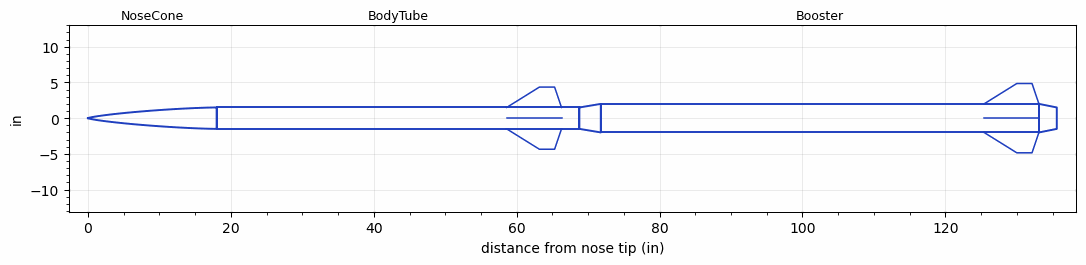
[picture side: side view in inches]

<RASAeroDocument>
 <FileVersion>2</FileVersion>
 <RocketDesign>
  <NoseCone>
   <Length>18</Length>
   <Diameter>3</Diameter>
   <Shape>Von Karman Ogive</Shape>
   <Location>0</Location>
  </NoseCone>
  <BodyTube>
   <Length>50.77</Length>
   <Diameter>3</Diameter>
   <Location>18</Location>
   <Fin>
    <Count>4</Count>
    <Chord>7.675</Chord>
    <Span>2.85</Span>
    <SweepDistance>4.579</SweepDistance>
    <TipChord>2.13</TipChord>
    <Thickness>0.125</Thickness>
    <LERadius>0.08</LERadius>
    <Location>10.175</Location>
    <AirfoilSection>Hexagonal</AirfoilSection>
    <FX1>0.22</FX1>
    <FX3>0.25</FX3>
   </Fin>
  </BodyTube>
  <Booster>
   <Length>61.32</Length>
   <Diameter>4</Diameter>
   <InsideDiameter>3</InsideDiameter>
   <Location>68.77</Location>
   <ShoulderLength>3</ShoulderLength>
   <BoattailLength>2.5</BoattailLength>
   <BoattailRearDiameter>3</BoattailRearDiameter>
   <Fin>
    <Count>4</Count>
    <Chord>7.675</Chord>
    <Span>2.85</Span>
    <SweepDistance>4.58</SweepDistance>
    <TipChord>2.13</TipChord>
    <Thickness>0.125</Thickness>
    <LERadius>0.08</LERadius>
    <Location>7.675</Location>
    <AirfoilSection>Hexagonal</AirfoilSection>
    <FX1>0.22</FX1>
    <FX3>0.25</FX3>
   </Fin>
  </Booster>
  <Surface>Rough Camouflage Paint</Surface>
  <ModifiedBarrowman>True</ModifiedBarrowman>
  <Turbulence>True</Turbulence>
  <UseBooster1>False</UseBooster1>
  <UseBooster2>False</UseBooster2>
 </RocketDesign>
 <LaunchSite>
  <Altitude>3000</Altitude>
  <Pressure>0</Pressure>
  <RodAngle>2</RodAngle>
  <RodLength>18</RodLength>
  <Temperature>85</Temperature>
  <WindSpeed>8</WindSpeed>
 </LaunchSite>
 <Recovery>
  <Altitude1>1000</Altitude1>
  <Altitude2>1000</Altitude2>
  <DeviceType1>None</DeviceType1>
  <DeviceType2>None</DeviceType2>
  <Event1>False</Event1>
  <Event2>False</Event2>
  <Size1>1</Size1>
  <Size2>1</Size2>
  <EventType1>None</EventType1>
  <EventType2>None</EventType2>
  <CD1>1.33</CD1>
  <CD2>1.33</CD2>
 </Recovery>
 <SimulationList>
  <Simulation>
   <SustainerEngine>L-1158  (L-1158)</SustainerEngine>
   <SustainerLaunchWt>20.8</SustainerLaunchWt>
   <SustainerNozzleDiameter>2.95</SustainerNozzleDiameter>
   <SustainerCG>41.16</SustainerCG>
   <SustainerIgnitionDelay>5</SustainerIgnitionDelay>
   <Booster1Engine>N-2857  (N-2857)</Booster1Engine>
   <Booster1LaunchWt>61.8</Booster1LaunchWt>
   <Booster1SeparationDelay>5</Booster1SeparationDelay>
   <Booster1IgnitionDelay>0</Booster1IgnitionDelay>
   <Booster1CG>79.81</Booster1CG>
   <Booster1NozzleDiameter>2.65</Booster1NozzleDiameter>
   <IncludeBooster1>True</IncludeBooster1>
   <Booster2Delay>0</Booster2Delay>
   <IncludeBooster2>False</IncludeBooster2>
   <TimetoApogee>59.00779</TimetoApogee>
   <MaxAltitude>50053.94</MaxAltitude>
   <MaxVelocity>2193.995</MaxVelocity>
  </Simulation>
 </SimulationList>
</RASAeroDocument>
